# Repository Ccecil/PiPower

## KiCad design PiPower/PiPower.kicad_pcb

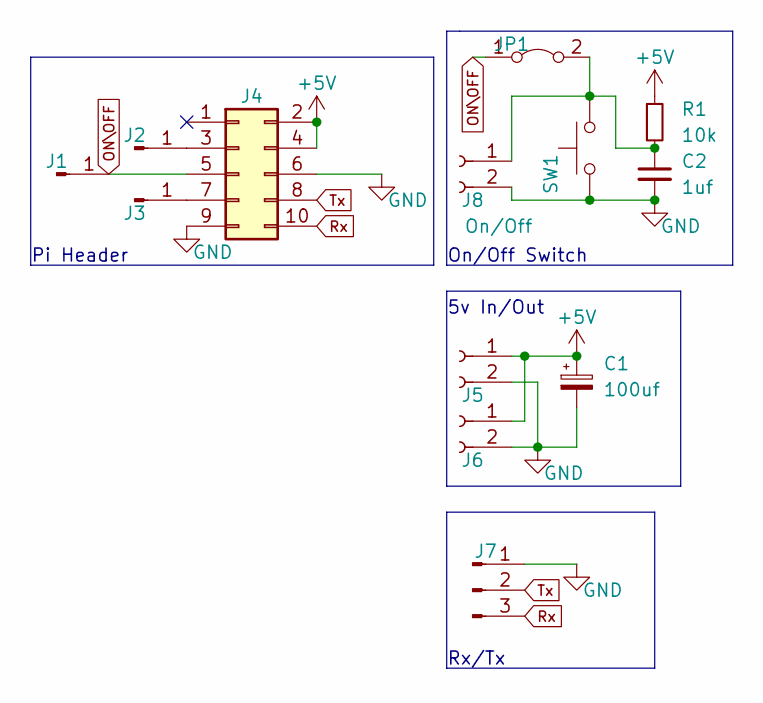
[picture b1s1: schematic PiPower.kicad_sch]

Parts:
C1: 100uf; CP_Elec_6.3x5.7
C2: 1uf; C_0402_1005Metric
J1, J2, J3: Conn_01x01_Male; PinHeader_1x01_P2.54mm_Vertical
J4: Conn_02x05_Odd_Even; PinHeader_2x05_P2.54mm_Vertical
J5: PowerIn; PhoenixContact_MSTBA_2,5_2-G-5,08_1x02_P5.08mm_Horizontal
J6: 5v Out; Molex_KK-254_AE-6410-02A_1x02_P2.54mm_Vertical
J7: Conn_01x03_Male; Molex_KK-254_AE-6410-03A_1x03_P2.54mm_Vertical
J8: On/Off; Molex_KK-254_AE-6410-02A_1x02_P2.54mm_Vertical
JP1: Jumper_2_Bridged; SolderJumper-2_P1.3mm_Bridged_RoundedPad1.0x1.5mm
R1: 10k; R_0402_1005Metric
SW1: SW_Push; SW_Push_SPST_NO_Alps_SKRK

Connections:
+5V: C1.1, J4.2, J4.4, J5.1, J6.1, R1.1
GND: C1.2, C2.2, J4.6, J4.9, J5.2, J6.2, J7.1, J8.2, SW1.1
unnamed: C2.1, J8.1, JP1.2 (B), R1.2, SW1.2
unnamed: J2.1, J4.3
unnamed: J3.1, J4.7
ON\OFF: J1.1, J4.5, JP1.1 (A)
Rx: J4.10, J7.3
Tx: J4.8, J7.2

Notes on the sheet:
Pi Header
Rx/Tx
5v In/Out
On/Off Switch

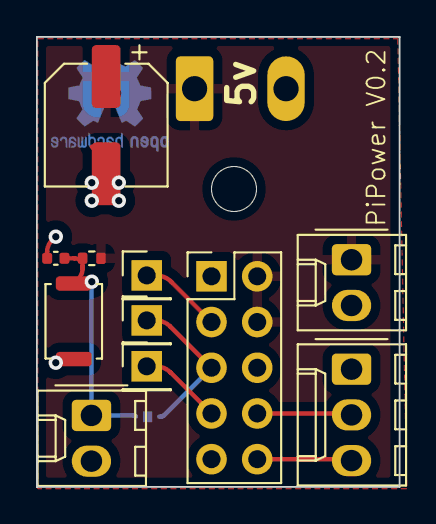
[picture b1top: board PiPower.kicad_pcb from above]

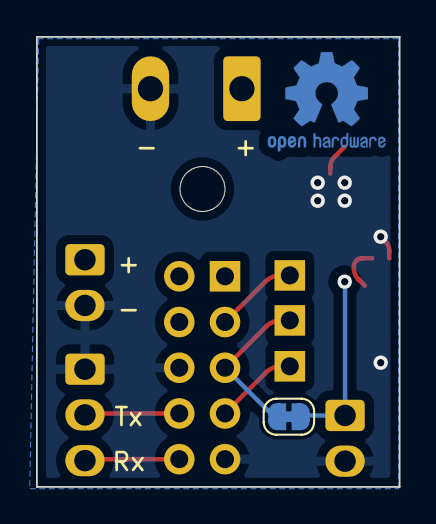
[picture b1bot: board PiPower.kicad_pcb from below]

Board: 2 copper layers, 20.1 x 25.0 mm, 13 parts (2 on the bottom side), 8 nets.

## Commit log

2022-01-03 Initial upload
    Prototype design. Not for production
